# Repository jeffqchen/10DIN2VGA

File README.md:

# 10DIN2VGA Multi-Purpose Dongle for Sega Saturn

This is a 10-pin mini DIN to VGA dongle that supports outputting RGBS or S-video & composite video signal, plus stereo audio, from a Sega Saturn.

The RGBS signal is compatible with 75-ohm terminated SCART video.

The S-video & composite video signals are directly output from the console.

This dongle belongs to my endeavour of [Console VGA Dongles Series](https://github.com/jeffqchen/Console-VGA-Dongle-Series/blob/main/README.md).

## Functionality

You need to decide the configuration of this dongle during assembly, by closing corresponding jumpers on the PCBs.

Due to the incompatibilities between the two configurations and the possibility of causing damage by mixing up the dongle and adapter, I decided not to include switches inside the dongle, but instead solder jumpers and clear marking on the outer shell.

### RGBS Configuration

The RGBS mode is the primary objective of this project.

When configured to RGBS mode, you can opt to use C-Sync when using with an NTSC console, or use either Luma or composite video as sync for compatibility with PAL consoles.

### S-Video/Composite Video Adapter Configuration (Optional)

When configured to adapter mode, you can use the widely available and cheap VGA to S-Video/CVBS adapter from Amazon to output the aformentioned video format.

Make sure the pinout of your adapter is as the following diagram:

*It is possible to modify the solder jumpers to change the adapter between the two configurations. However it's not recommended to repeatedly taking this dongle apart for that purpose, as the structural integrity might become compromised.*

## Design Details

The 10-pin mini DIN connector on the Sega Saturn has several problems.

The biggest one is that there is only one correct way to insert it, and infinite wrong ways to attempt. There is also no easy way to tell whether you are holding it correctly without triple checking with your eyes. It's also very difficult to maintain the correct orientation during insertion, even after you've confirmed it.

Most 10-pin DIN ports on the Saturn are badly damaged due to bad attempts to insert a video cable. Combined with too much force applied, the connector is frequently broken.

Due to the position of the port, the strain from the video cable will stress the connector and make the connection unreliable, or even reduce the life of the port and/or the cable.

The design of this dongle eliminates all the aforementioned problems.

The shape of the outside shell makes it easy to tell which way it's facing. Make sure the curve is in the 2nd quadrant and you know it's the correct way.

The shape of the inside shell conforms to the indented area around the AV port on the console, with the bottom of the dongle flat and flush with the table. This will ensure there is only one way to plug in the adapter. Since the adapter tightly follows the outline of the shell, rotational stress and downward stress are effectively offloaded to the shell of the console, as well as making it impossible to insert the connector too far into the console.

The VGA port stands vertically, which ensures that it's strong against downward stress itself, as well as avoiding a rotationally pulling tendency that could pull the 10-pin DIN connector out of the console.

The optional 3.5mm audio jack was carefully positioned so that it doesn't block the communication port.

The power jack was also avoided, including the launch version with a slightly protruding profile.

## Parts

- Project PCB
  - [Main Board](https://oshpark.com/projects/ftX4cA6v)
  - [VGA Board](https://oshpark.com/projects/xInxeNXi)
  
- 3D Printed Shell
  - [Front Shell (Universal)](https://github.com/jeffqchen/10DIN2VGA/blob/main/3D%20Print/Shell%20Front.stl)
  - Back Shell (Choose one according to your configuration)
    - [RGBS Marking](https://github.com/jeffqchen/10DIN2VGA/blob/main/3D%20Print/Shell%20Back-RGB.stl)
    - [Y/C & C Marking](https://github.com/jeffqchen/10DIN2VGA/blob/main/3D%20Print/Shell%20Back-YC.stl)
    - [No Marking](https://github.com/jeffqchen/10DIN2VGA/blob/main/3D%20Print/Shell%20Back.stl)
  - [Insert](https://github.com/jeffqchen/10DIN2VGA/blob/main/3D%20Print/Insert.stl)

- VGA Port Slim, Female - [Link](https://github.com/jeffqchen/JeffParts/blob/main/Connectors/HD15/Slim/Female%20PCB/info.md)

- 10 pin Mini DIN Male Plug, Through-Hole Type - [Link](https://github.com/jeffqchen/JeffParts/blob/main/Connectors/Mini%20DIN/10Pin/Through%20Hole/info.md)

- 3.5mm Headphone Jack, Vertical - [Link](https://github.com/jeffqchen/JeffParts/blob/main/Connectors/3.5mm%20Audio%20Jack/Vertical%205-Pin%20PCB/info.md)

- [2x] SMD Capacitor, 10uF / 6.3V / Imperial 0603 Size

- M2-16mm screw and hex nut - [Link](https://github.com/jeffqchen/JeffParts/blob/main/Parts/M2%20M3%20Hex%20Screw%20%26%20Nut/info.md)

### Optional

For CSync configuration on NTSC console
- SMD Capacitor, 220uF / 6.3V / Imperial 1206 Size - [Link](https://github.com/jeffqchen/JeffParts/blob/main/Components/220uF%20SMD%20Cap/info.md)

- SMD Resistor, 470 Ohm / Imperial 0603 Size

## 3D Printing

Print the parts in the orientation shown below. Support is required and must be completely removed after wards.

### Preparing After Printing

#### Front Shell

There will be a small piece of support material stuck inside the cavity designed for a hidden nut.

You must extract that piece of support material in order for the nut to go in.

A dental pick will work nicely. A pair of tweezers with sharp tips might work as well.

After extracting ALL the support material (check with a flashlight), press and fit the M2 nut inside. It might be a tight fit.

#### Back Shell

Make sure the barrel cavity for the 10-pin DIN connector is smooth. If you see any artifact or blob sticking into the hole, trim with a sharp knife.

## Assembly

### Preparing the PCB

Trim all the stubs sticking out side the PCB profile. Side cutters and files are your friends.

### Combine the Two PCBs

The Two PCBs must be combined in a perfect perpendicular shape. With the help of the 3D printed insert piece, you can easily get this done.

Start by inserting the VGA board all the way into the slot in the main board. There should be NO gap.

Insert the combined PCBs into the slot in the printed insert piece.

Solder in one pin and check if the PCBs are perfectly perpendicular to each other and have no gap between each other. Adjust by re-melting the joint.

After confirming, remove the insert and solder in the castellated vias, one side at a time.

Add ample amount of solder and make sure all the joints are nice and full.

### Solder SMD Components

Tin SMD pads for the capacitors and resistors, and solder them in place.

**If you are planning to NOT use CSync, or if your console is PAL, do NOT populate the two components inside the "CSYNC NTSC" area.**

### Solder VGA Port

Nothing Special, just make sure it's all the way flush to the VGA board.

### Solder 10-pin Mini DIN Port

Pre-tin the two curvy ground pads around the 10DIN footprint on the "Saturn Side" of the main board with a small amount of solder, then wick them clean. Make sure the pads are as flat as possbile.

Insert the 10DIN port **all the way** into the PCB from the "Saturn Side" of the main board. Make sure there is no gap between the 10DIN connector and the main board.

Solder down the tongue on the top of the DIN with some solder, so the connector stays in place.

Add some solder to the curvy ground pads around the 10DIN. Make sure the solder is well-wetted to both the pads and the metal shielding.

*You might have to raise the temperature of your iron by a few dozens of degrees in Celsius if you usually solder at a lower temperature. I went from 370 to 400.*

Solder in all the pins on the other side.

**Do NOT heat up these pins for too long or you risk melting plastic holding the pins inside the connector and destroying it.**

Add more solder to the top tongue and make sure solder creeps over to the other side of the PCB to form a strong joint by keeping the heat on for a bit longer.

### Configure The Jumpers

#### RGBS Mode

Close the jumpers to the lower position (with triangle) on the main board. Do NOT close the jumper on the VGA board.

If you wish to use alternative sync signals (Luma OR CVBS), close the corresponding jumper inside the "Alt-Sync" area as well. **Do NOT close both of them.**

#### Adapter Mode
Close the jumpers to the upper position (without triangle) on the main board. Close the jumper on the VGA board.

### Solder 3.5mm Audio Jack

Insert the 3.5mm audio jack into the main PCB from the "Outside".

Make sure it's flush to the PCB, then solder in two pins with a small amount of solder.

Trim all the protruding legs. Make sure they are as short as possible, but there's no need to go crazy to make it flush.

Solder in all the pins with proper amounts of solder.

### Closing The Shell

Start by inserting the 10-pin DIN into the shell from the inside.

This will be a tight fit. Try pressing straight down from the back of the DIN connector to avoid lateral movements.

If it's difficult, use the insert piece as a thumb guard as below.

The insert piece should be left inside the shell as a support piece. It should be flush or below the shell interface. If it's sticking out, the board assembly is not in place.

Push down the PCB all the way. Use the 3.5mm jack as a reference. The port should touch the shell when the board assembly is in place.

Close the front shell onto the assembly. Hold the shells together with one hand, and put the M2-16mm screw in.

When it begins to feel harder to turn the screw driver, start using only 3 fingers to turn the screw driver in order to prevent over-tightening it and cracking the front shell.

The screw head should be flush or slightly below the back surface of the dongle as shown below.

And you have built the dongle!

#### Double Down On Strength

I've left a few gaps around the 10-pin DIN connector barrel. You may inject small amounts of super glue or even epoxy to make it indestructible. I didn't feel the necessity personally, but just in case your printer came out with a piece that's slightly loose.

#### If the 10-pin DIN Barrel Was Impossible To Push In

Your printer might give you a print with the barrel cavity being too tight. You can try using "Hole Horizontal Expansion" in Cura (or an equivalent option in other slicer software) to give it a 0.1mm expansion.

----------------
Shield: [![CC BY-NC-SA 4.0][cc-by-nc-sa-shield]][cc-by-nc-sa]

This work is licensed under a
[Creative Commons Attribution-NonCommercial-ShareAlike 4.0 International License][cc-by-nc-sa].

[![CC BY-NC-SA 4.0][cc-by-nc-sa-image]][cc-by-nc-sa]

[cc-by-nc-sa]: http://creativecommons.org/licenses/by-nc-sa/4.0/
[cc-by-nc-sa-image]: https://licensebuttons.net/l/by-nc-sa/4.0/88x31.png
[cc-by-nc-sa-shield]: https://img.shields.io/badge/License-CC%20BY--NC--SA%204.0-lightgrey.svg

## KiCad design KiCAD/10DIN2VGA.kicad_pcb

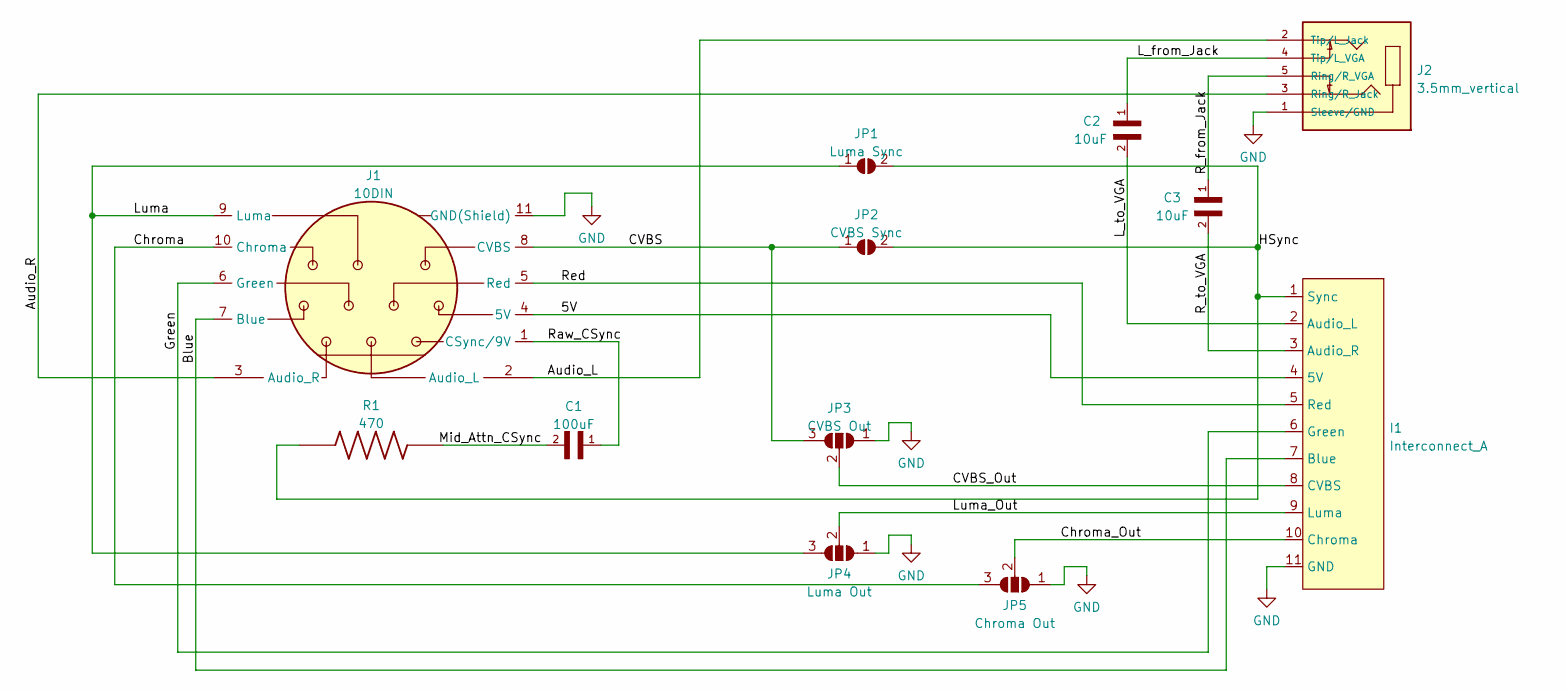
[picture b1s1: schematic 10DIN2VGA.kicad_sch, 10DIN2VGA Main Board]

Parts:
C1: 100uF; C_1206_3216Metric_Pad1.33x1.80mm_HandSolder
C2, C3: 10uF; C_0603_1608Metric_Pad1.08x0.95mm_HandSolder
I1: Interconnect_A
J1: 10DIN
J2: 3.5mm_vertical; PARTREV 1.01
JP1: Luma Sync; SolderJumper-2_P1.3mm_Open_RoundedPad1.0x1.5mm
JP2: CVBS Sync; SolderJumper-2_P1.3mm_Open_RoundedPad1.0x1.5mm
JP3: CVBS Out; SolderJumper-3_P1.3mm_Open_RoundedPad1.0x1.5mm
JP4: Luma Out; SolderJumper-3_P1.3mm_Open_RoundedPad1.0x1.5mm
JP5: Chroma Out; SolderJumper-3_P1.3mm_Open_RoundedPad1.0x1.5mm
R1: 470; R_0603_1608Metric_Pad0.98x0.95mm_HandSolder

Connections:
/5V: I1.4 (5V), J1.4 (5V)
/Audio_L: J1.2 (Audio_L), J2.2 (Tip/L_Jack)
/Audio_R: J1.3 (Audio_R), J2.3 (Ring/R_Jack)
/Blue: I1.7 (Blue), J1.7 (Blue)
/CVBS: J1.8 (CVBS), JP2.1 (A), JP3.3 (B)
/CVBS_Out: I1.8 (CVBS), JP3.2 (C)
/Chroma: J1.10 (Chroma), JP5.3 (B)
/Chroma_Out: I1.10 (Chroma), JP5.2 (C)
/Green: I1.6 (Green), J1.6 (Green)
/HSync: I1.1 (Sync), JP1.2 (B), JP2.2 (B), R1.1
/L_from_Jack: C2.1, J2.4 (Tip/L_VGA)
/L_to_VGA: C2.2, I1.2 (Audio_L)
/Luma: J1.9 (Luma), JP1.1 (A), JP4.3 (B)
/Luma_Out: I1.9 (Luma), JP4.2 (C)
/Mid_Attn_CSync: C1.2, R1.2
/R_from_Jack: C3.1, J2.5 (Ring/R_VGA)
/R_to_VGA: C3.2, I1.3 (Audio_R)
/Raw_CSync: C1.1, J1.1 (CSync/9V)
/Red: I1.5 (Red), J1.5 (Red)
GND: I1.11 (GND), J1.11 (GND(Shield)), J2.1 (Sleeve/GND), JP3.1 (A), JP4.1 (A), JP5.1 (A)

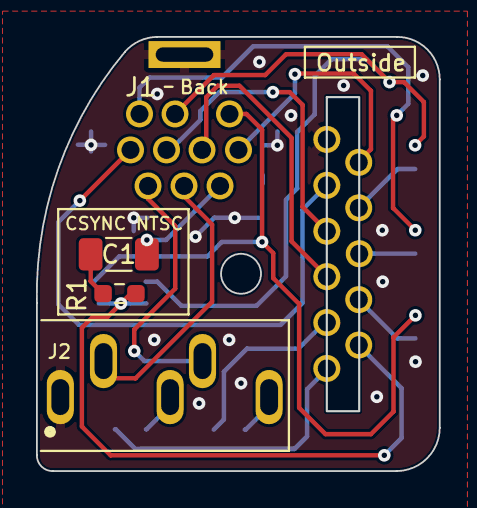
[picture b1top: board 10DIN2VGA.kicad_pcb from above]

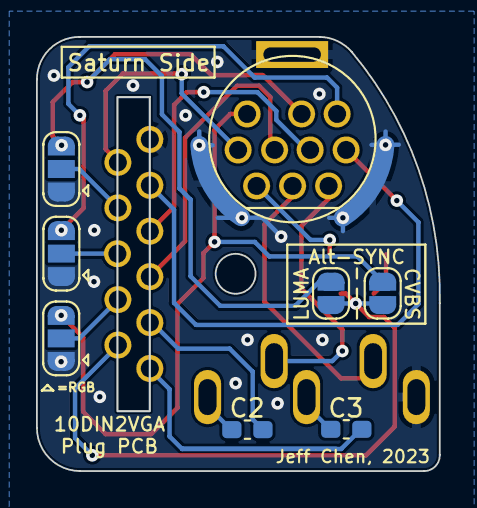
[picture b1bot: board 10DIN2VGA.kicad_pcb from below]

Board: 2 copper layers, 22.4 x 24.1 mm, 12 parts (7 on the bottom side), 20 nets.

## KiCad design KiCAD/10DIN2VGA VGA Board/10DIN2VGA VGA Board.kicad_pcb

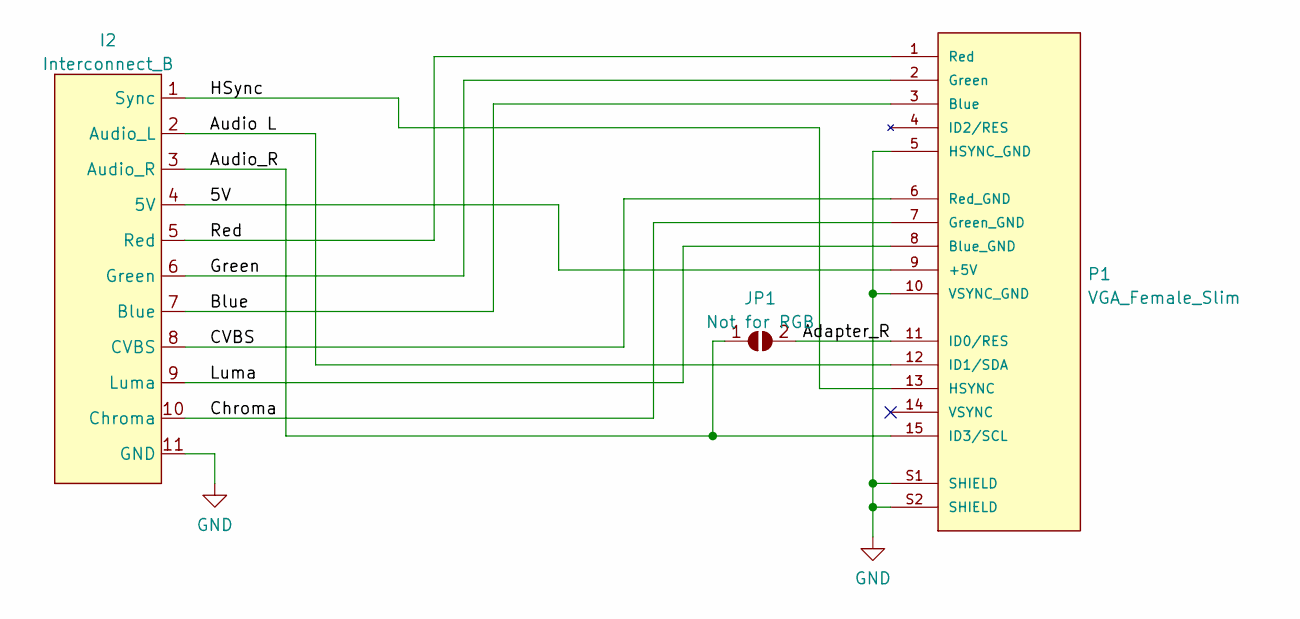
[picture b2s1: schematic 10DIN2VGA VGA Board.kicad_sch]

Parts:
I2: Interconnect_B
JP1: Not for RGB; SolderJumper-2_P1.3mm_Open_RoundedPad1.0x1.5mm
P1: VGA_Female_Slim; VGA_female_rightangle_slim; PARTREV N/A

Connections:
/5V: I2.4 (5V), P1.9 (+5V)
/Adapter_R: JP1.2 (B), P1.11 (ID0/RES)
/Audio L: I2.2 (Audio_L), P1.12 (ID1/SDA)
/Audio_R: I2.3 (Audio_R), JP1.1 (A), P1.15 (ID3/SCL)
/Blue: I2.7 (Blue), P1.3 (Blue)
/CVBS: I2.8 (CVBS), P1.6 (Red_GND)
/Chroma: I2.10 (Chroma), P1.7 (Green_GND)
/Green: I2.6 (Green), P1.2 (Green)
/HSync: I2.1 (Sync), P1.13 (HSYNC)
/Luma: I2.9 (Luma), P1.8 (Blue_GND)
/Red: I2.5 (Red), P1.1 (Red)
GND: I2.11 (GND), P1.5 (HSYNC_GND), P1.10 (VSYNC_GND), P1.S1 (SHIELD), P1.S2 (SHIELD)

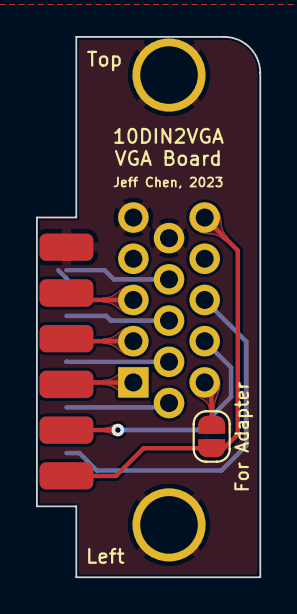
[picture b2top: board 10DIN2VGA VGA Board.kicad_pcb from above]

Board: 2 copper layers, 12.4 x 30.0 mm, 3 parts (1 on the bottom side), 12 nets.

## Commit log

2023-01-06 Files
2023-01-06 Add pictures
2023-01-06 Modify pics
2023-01-06 Modifications
2023-01-06 Writing readme
2023-01-06 Write Readme
2023-01-06 Rename license file
2023-01-06 更新 README.md
2023-01-07 Update Back Shell Design
2023-09-14 Revert "Delete cover.jpg"
    This reverts commit 5d6e8106d7c5ed9e6e1f0860eb3e58afa1c729a1.
